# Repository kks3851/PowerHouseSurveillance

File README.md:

# Power-House-Surveillance 

Webcam for tracking of faces, and system wake up from motion detection and website
Project Made in EECS 495 - Engineering System Design 2, Spring 2017 at Northwestern University

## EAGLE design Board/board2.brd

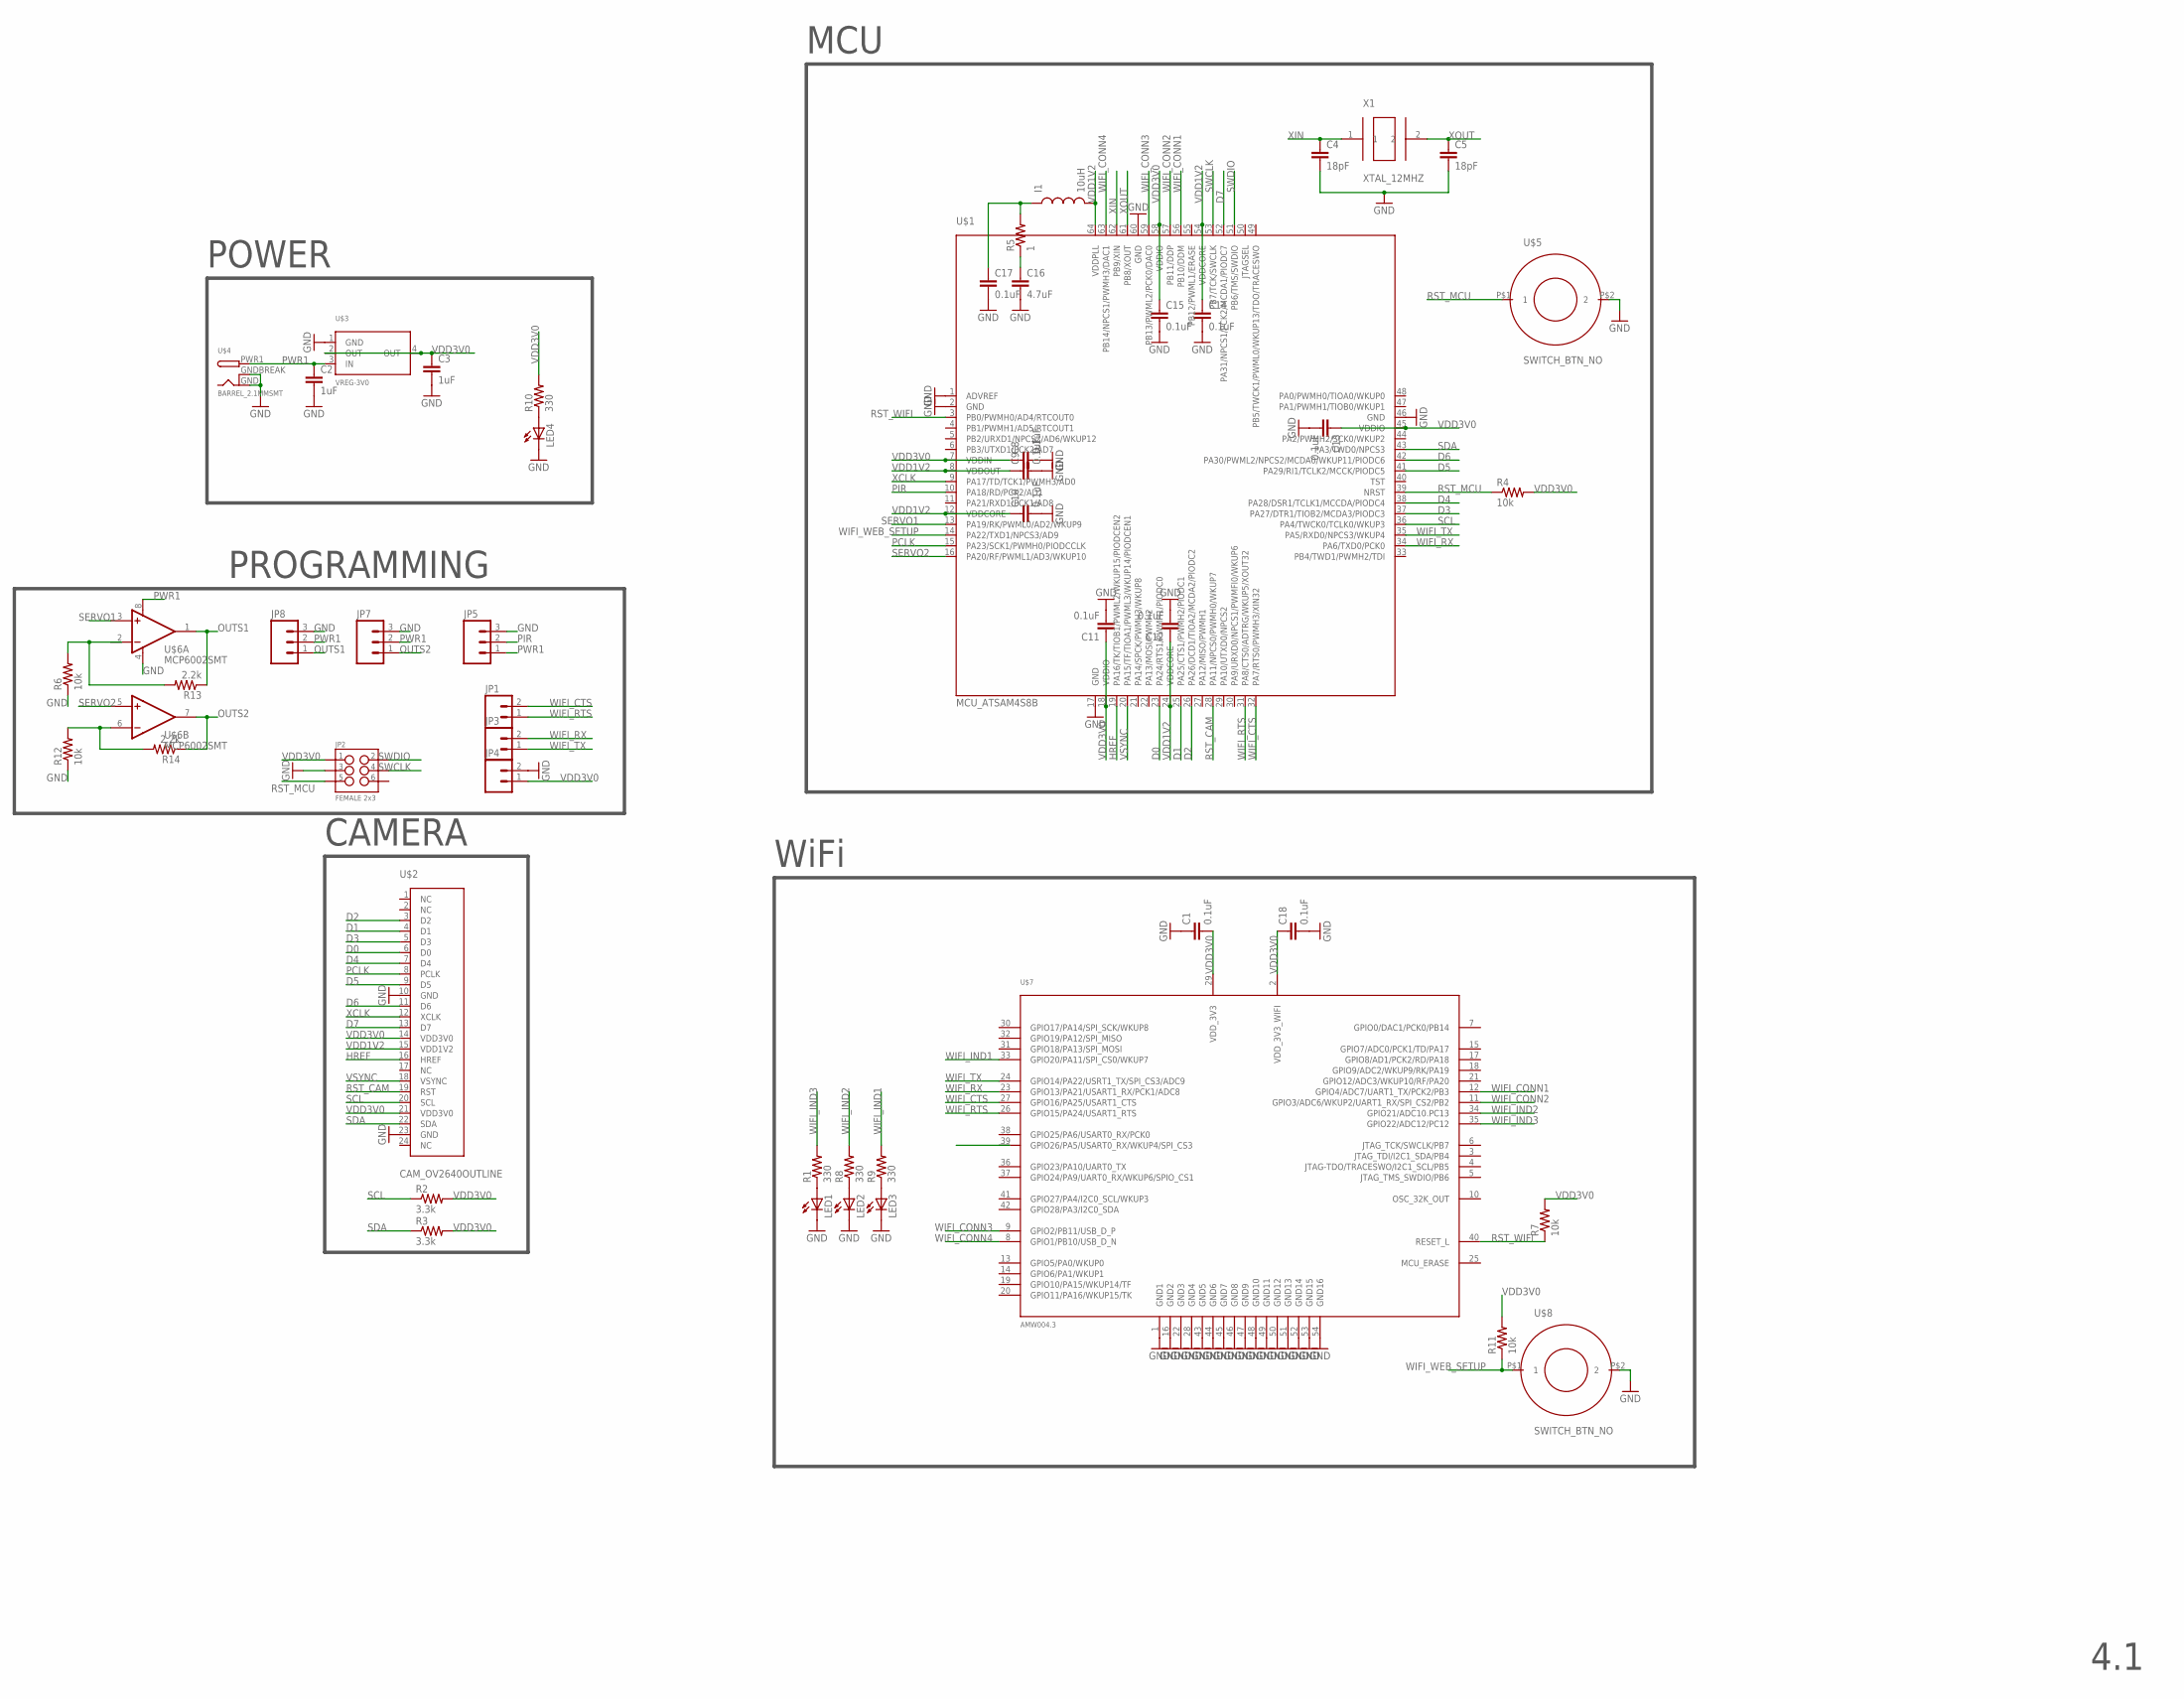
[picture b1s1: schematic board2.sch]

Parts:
C1, C8, C9, C10, C11, C12, C13, C14, C15, C17, C18: 0.1uF; 0805
C2, C3: 1uF; 0805
C4, C5: 18pF; 0805
C16: 4.7uF; 0805
I1: 10uH; 0805
JP1, JP3, JP4: M02PTH; 1X02
JP2: FEMALE 2x3; 2X3
JP5, JP7, JP8: M03LOCK; 1X03_LOCK
LED1, LED2, LED3, LED4: LED0603; LED-0603
R1, R8, R9, R10: 330; 0805
R2, R3: 3.3k; 0805
R4, R6, R7, R11, R12: 10k; 0805
R5: 1; 0805
R13, R14: 2.2k; 0805
U$1: MCU_ATSAM4S8B; QFP50P1200X1200X160-64N
U$2: CAM_OV2640OUTLINE; CAM_CONN
U$3: VREG-3V0; R-PDSO-G4_TI
U$4: BARREL_2.1MMSMT; DCJACK_2MM_SMT
U$5, U$8: SWITCH_BTN_NO; BTN_2
U$6: MCP6002SMT; SOIC8
U$7: AMW004.3; AMW004
X1: XTAL_12MHZ; ABM7-16.000MHZ-D2Y-T

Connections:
D0: U$1.23 (PA24/RTS1/PWMH1/PIODC0), U$2.6 (D0)
D1: U$1.25 (PA25/CTS1/PWMH2/PIODC1), U$2.4 (D1)
D2: U$1.26 (PA26/DCD1/TIOA2/MCDA2/PIODC2), U$2.3 (D2)
D3: U$1.37 (PA27/DTR1/TIOB2/MCDA3/PIODC3), U$2.5 (D3)
D4: U$1.38 (PA28/DSR1/TCLK1/MCCDA/PIODC4), U$2.7 (D4)
D5: U$1.41 (PA29/RI1/TCLK2/MCCK/PIODC5), U$2.9 (D5)
D6: U$1.42 (PA30/PWML2/NPCS2/MCDA0/WKUP11/PIODC6), U$2.11 (D6)
D7: U$1.52 (PA31/NPCS1/PCK2/MCDA1/PIODC7), U$2.13 (D7)
GND: C1.1, C2.2, C3.2, C4.2, C5.2, C8.2, C9.2, C10.2, C11.2, C12.2, C13.2, C14.2, C15.2, C16.2, C17.2, C18.2, JP2.3, JP4.2, JP5.3, JP7.3, JP8.3, LED1.C, LED2.C, LED3.C, LED4.C, R6.1, R12.1, U$1.1 (ADVREF), U$1.2 (GND), U$1.17 (GND), U$1.46 (GND), U$1.60 (GND), U$2.10 (GND), U$2.23 (GND), U$3.1 (GND), U$4.GND, U$4.GNDBREAK, U$5.P$2 (2), U$6.4 (V-), U$7.1 (GND1), U$7.16 (GND2), U$7.22 (GND3), U$7.28 (GND4), U$7.43 (GND5), U$7.44 (GND6), U$7.45 (GND7), U$7.46 (GND8), U$7.47 (GND9), U$7.48 (GND10), U$7.49 (GND11), U$7.50 (GND12), U$7.51 (GND13), U$7.52 (GND14), U$7.53 (GND15), U$7.54 (GND16), U$8.P$2 (2)
HREF: U$1.19 (PA16/TK/TIOB1/PWML2/WKUP15/PIODCEN2), U$2.16 (HREF)
unnamed: C17.1, I1.1, R5.2
unnamed: C16.1, R5.1
unnamed: LED1.A, R1.1
unnamed: LED2.A, R8.1
unnamed: LED3.A, R9.1
unnamed: LED4.A, R10.1
unnamed: R6.2, R13.2
unnamed: R12.2, R14.2, U$6.6 (-IN)
OUTS1: JP8.1, R13.1, U$6.1 (OUT)
OUTS2: JP7.1, R14.1, U$6.7 (OUT)
PCLK: U$1.15 (PA23/SCK1/PWMH0/PIODCCLK), U$2.8 (PCLK)
PIR: JP5.2, U$1.10 (PA18/RD/PCK2/AD1)
PWR1: C2.1, JP5.1, JP7.2, JP8.2, U$3.3 (IN), U$4.PWR1 (PWR), U$6.8 (V+)
RST_CAM: U$1.28 (PA11/NPCS0/PWMH0/WKUP7), U$2.19 (RST)
RST_MCU: JP2.5, R4.1, U$1.39 (NRST), U$5.P$1 (1)
RST_WIFI: R7.1, U$1.3 (PB0/PWMH0/AD4/RTCOUT0), U$7.40 (RESET_L)
SCL: R2.1, U$1.36 (PA4/TWCK0/TCLK0/WKUP3), U$2.20 (SCL)
SDA: R3.1, U$1.43 (PA3/TWD0/NPCS3), U$2.22 (SDA)
SERVO1: U$1.13 (PA19/RK/PWML0/AD2/WKUP9), U$6.3 (+IN)
SERVO2: U$1.16 (PA20/RF/PWML1/AD3/WKUP10), U$6.5 (+IN)
SWCLK: JP2.4, U$1.53 (PB7/TCK/SWCLK)
SWDIO: JP2.2, U$1.51 (PB6/TMS/SWDIO)
VDD1V2: C9.1, C10.1, C12.1, C14.1, I1.2, U$1.8 (VDDOUT), U$1.12 (VDDCORE), U$1.24 (VDDCORE), U$1.54 (VDDCORE), U$1.64 (VDDPLL), U$2.15 (VDD1V2)
VDD3V0: C1.2, C3.1, C8.1, C11.1, C13.1, C15.1, C18.1, JP2.1, JP4.1, R2.2, R3.2, R4.2, R7.2, R10.2, R11.2, U$1.7 (VDDIN), U$1.18 (VDDIO), U$1.45 (VDDIO), U$1.58 (VDDIO), U$2.14 (VDD3V0), U$2.21 (VDD3V0), U$3.2 (OUT), U$3.4 (OUT), U$7.2 (VDD_3V3_WIFI), U$7.29 (VDD_3V3)
VSYNC: U$1.20 (PA15/TF/TIOA1/PWML3/WKUP14/PIODCEN1), U$2.18 (VSYNC)
WIFI_CONN1: U$1.56 (PB10/DDM), U$7.12 (GPIO4/ADC7/UART1_TX/PCK2/PB3)
WIFI_CONN2: U$1.57 (PB11/DDP), U$7.11 (GPIO3/ADC6/WKUP2/UART1_RX/SPI_CS2/PB2)
WIFI_CONN3: U$1.59 (PB13/PWML2/PCK0/DAC0), U$7.9 (GPIO2/PB11/USB_D_P)
WIFI_CONN4: U$1.63 (PB14/NPCS1/PWMH3/DAC1), U$7.8 (GPIO1/PB10/USB_D_N)
WIFI_CTS: JP1.2, U$1.32 (PA7/RTS0/PWMH3/XIN32), U$7.27 (GPIO16/PA25/USART1_CTS)
WIFI_IND1: R9.2, U$7.33 (GPIO20/PA11/SPI_CS0/WKUP7)
WIFI_IND2: R8.2, U$7.34 (GPIO21/ADC10.PC13)
WIFI_IND3: R1.2, U$7.35 (GPIO22/ADC12/PC12)
WIFI_RTS: JP1.1, U$1.31 (PA8/CTS0/ADTRG/WKUP5/XOUT32), U$7.26 (GPIO15/PA24/USART1_RTS)
WIFI_RX: JP3.2, U$1.34 (PA6/TXD0/PCK0), U$7.23 (GPIO13/PA21/USART1_RX/PCK1/ADC8)
WIFI_TX: JP3.1, U$1.35 (PA5/RXD0/NPCS3/WKUP4), U$7.24 (GPIO14/PA22/USRT1_TX/SPI_CS3/ADC9)
WIFI_WEB_SETUP: R11.1, U$1.14 (PA22/TXD1/NPCS3/AD9), U$8.P$1 (1)
XCLK: U$1.9 (PA17/TD/TCK1/PWMH3/AD0), U$2.12 (XCLK)
XIN: C4.1, U$1.62 (PB9/XIN), X1.1
XOUT: C5.1, U$1.61 (PB8/XOUT), X1.2

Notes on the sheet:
POWER
PROGRAMMING
CAMERA
WiFi
MCU
4.1

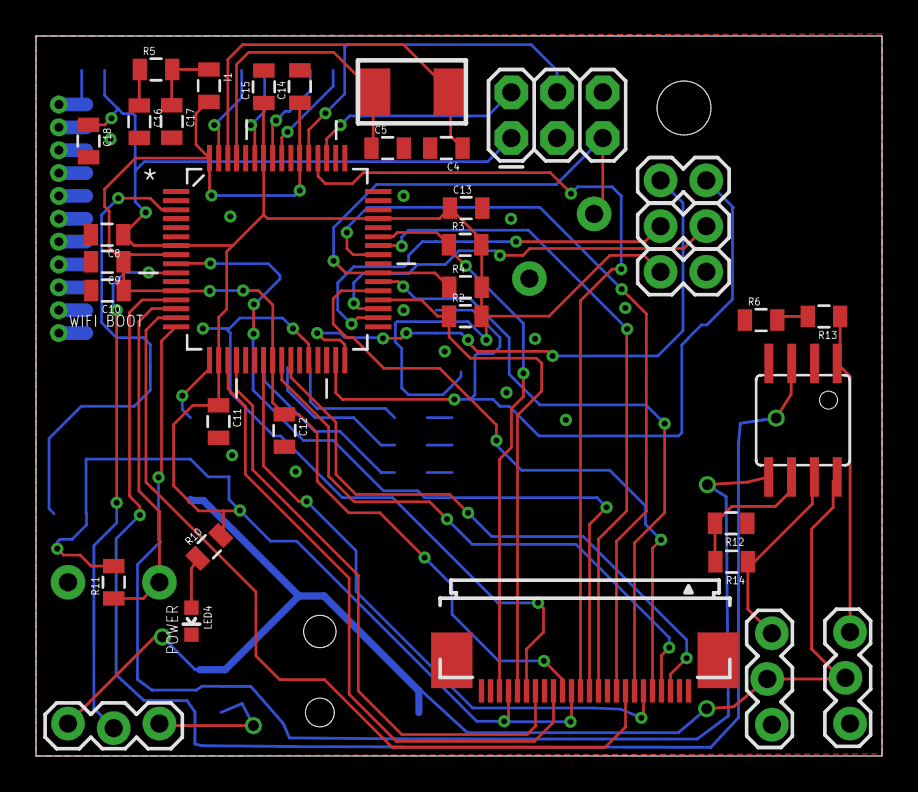
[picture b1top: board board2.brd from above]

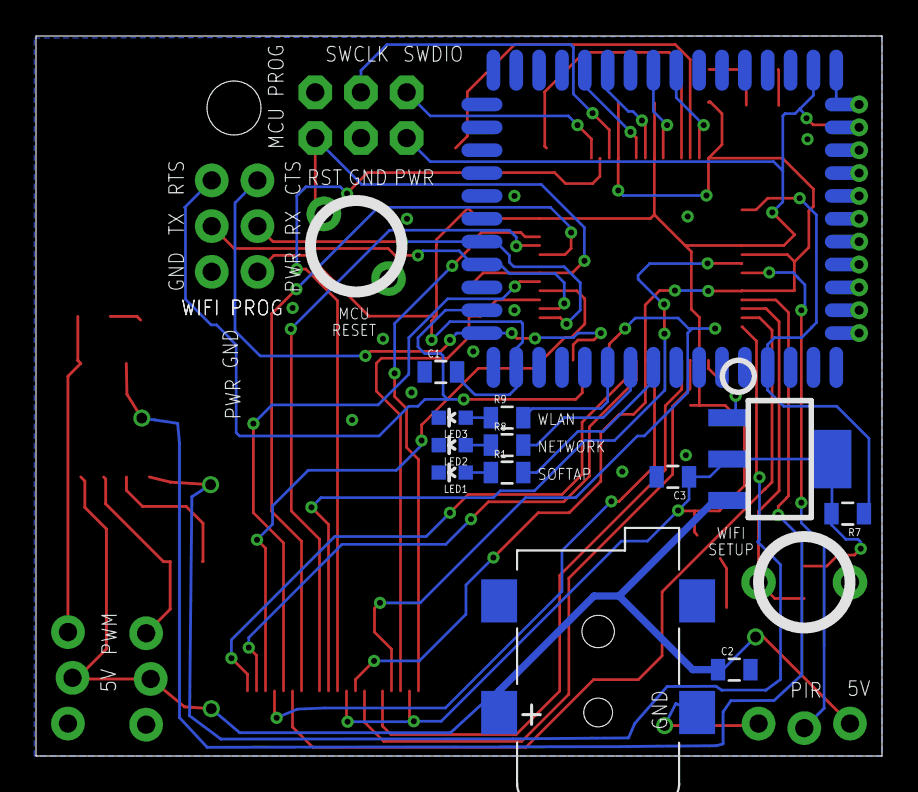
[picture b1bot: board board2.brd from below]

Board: 2 copper layers, 47.0 x 40.0 mm, 51 parts (15 on the bottom side), 50 nets.

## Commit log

2017-11-30 Power House Surveillance

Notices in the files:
parts and their libraries:
SparkFun: Licensing: CC v3.0 Share-Alike You are welcome to use this library for commercial purposes.
SparkFun-Connectors: Licensing: Creative Commons ShareAlike 4.0 International - https://creativecommons.org/licenses/by-sa/4.0
